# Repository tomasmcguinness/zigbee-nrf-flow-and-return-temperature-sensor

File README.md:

# Zigbee Flow and Return Temperature Sensor on nRF52840

A Zigbee Sensor designed to monitor flow and return temperatures. The sensor provides two temperature sensor probes in a single unit. It can be used to monitor a boiler's flow and return temperatures or the difference between the tails of a radiator.

It uses two NTC Thermistors, which can be attached to the flow and return pipes on whatever you wish to measure; radiator tails, boiler flow and return, hot water cylinder. 

Battery powered, this sensor should run for over about a year and a half on a coin battery or around ten years on a 2000mAh battery.

> [!IMPORTANT] 
> This is still a work in progress. I have included a short list of items at the end of this README

## Parts

* 1 x Seeed XIAO nRF52840
* 2 x 10kΩ 0.1% resistors
* 2 x NTC Thermistors (I use these TT0P-10KC3-T105-1500)
* 1 x push button

## Wiring

In the diagram below, you would replace the two 10kΩ thermistor that are not on the breadboard with the actual probes

## Compiling 

This code has been developed using NCS (nRF Connect Software), with pin outs and battery reading chosen for the Seeed XIAO nrf52840. It should run on any nRF52840 with some tweaking. There is an overlay included for the nRF52840DK, which I use for development.

To compile, run the following command in an `nRF Connect` terminal. The pristine build (-p) flag isn't always necessary.

```
west build -b xiao_ble -p
```

## Flashing

The XIAO board can be flashed using two methods. The first is done using the factory installed bootloader. The second is done using a J-Link programmer. I have a J-Link programmer, so that's the method I've been using.

### UF2

> [!CAUTION] 
> Whilst this method *should* work, I haven't have any success! I want to make this project accessible to those without a J-Link, so I will dedicate time to it.

First, connect the board via USB to your computer. Next, double click the Reset button. A new USB drive should appear.

The compilation process will generate a UF2 firmware file and it will be be located here:

```
zigbee-nrf-flow-and-return-temperature-sensor\build\zigbee-nrf-flow-and-return-temperature-sensor\zephyr\zephyr.uf2
```

Just copy and paste this file onto the USB drive and the application *should* start. 

### J-Link

If you have a J-Link programmer, connect the board and run this command.

```
west flash
```

## Pairing

Once you have flashed the nRF52840 and powered it up, it will enter pairing mode. You can then add it to your Zigbee network using your usual method.

# NTC Thermistors

My Zigbee sensor was build with the TT0P-10KC3-T105-1500 probes, as I have already mentioned. These have a nominal resistance of 10kΩ @ 25°C and have a beta value of 3977. The relevant definitions in the code are here.

```
#define THERMISTORNOMINAL 10000
#define TEMPERATURENOMINAL 25
#define BCOEFFICIENT 3977
#define SERIESRESISTOR 10000
```

> [!NOTE] 
> If you want to use a different thermistor, you can change these values. I plan on making these configurable via the project, but for now you will need to change them directly in code.

# GPIOs

There several GPIOs configured by this project. These have been picked for the Seeed XIAO nRF52840 board.

| GPIO  | Usage |
| ------------- | ------------- |
| P0.03 | ADC (AIN1) pin for Probe 1  |
| P0.29 | ADC (AIN5) pin for Probe 2  |
| P0.28 | Power for the voltage dividers connected to the NTC temperature probes |
| P1.13 | Reset pin. Apply high for 10 seconds to reset the Zigbee configuration | 

# Zigbee ZCL

In order to maintain compatability, this sensor uses standard ZCL clusters rather.

There are three Endpoints 1, 5 & 7

Endpoint 1 contains the Basic cluster, the Identify Cluster and the Power Configuration Cluster.
Endpoint 5 contains a Temperature Measurement Cluster
Endpoint 7 contains a Temperature Measurement Cluster

# Home Assistant

I have tested my sensor on HomeAssistant using the ZHA integration and it displays pretty well. 

Unfortunately, the probe names are terrible.

```
sensor.coldbear_fart_sensor_temperature
sensor.coldbear_fart_sensor_temperature_2
```

I have tried to make a ZHA "Quirk" to display the probes like this:

```
sensor.coldbear_fart_sensor_flow_temperature
sensor.coldbear_fart_sensor_return_temperature
```

but I haven't had any success yet making it work how I want. I have included my work in progress in the project.

# Battery Life

I've invested a lot of time to try and ensure long battery life and I think I've gotten it to over a year on a coin battery! Average consumption is around 16µA

I've written quite a few blog posts detailing the journey, which are up on my blog. You can start here:

https://tomasmcguinness.com/2024/12/19/reducing-power-consumption-in-my-nrf52840-zigbee-sensor-with-the-help-of-a-nordic-semiconductors-power-profiler-ii-kit/

# Setup

Once powered up, you can add the device to your Zigbee network as you would any other Zigbee device.

# PCB

Using KiCAD, I have designed a PCB for this code. 

## V2
A mix of SMD and throughhole mountings, this revision fixes the traces for the reset button (issue in V1) and uses updated footprints for the JST connectors.

> [!CAUTION]
> The battery connections on this PCB are just very difficult to make. I've tried on three different boards, but I've not managed to power the XIAO using the battery terminal. If you had a finer soldering iron, you might have better luck.

## V3
To work around the battery terminal issue and make it easier to for amateurs like myself to solder, V3 has switched to a socket mount for the XIAO board. I also hope to use pogo pins to make the battery connections.

> [!NOTE]
> As of the 15th Feb 2025, I am waiting on the first fabricated versions of this board to verify the socket and pogo pin design will work. 

## V4
This is incomplete. The goal is to move to SMD mounting compleletely and introduce a CR2032 battery holder to make the unit complete. It's present in the PCB-V4 branch.

> [!CAUTION]
> V4 is a work in progress and not ready for use!

All the external connections for NTC probes and battery are via JST connectors.

If you are interested in buying a PCB, do let me know. If there is enough interest, I can place a bulk order.

# Support

If you want to support this project, please consider buying me a coffee!

# Next Steps

* [x] ~~Fix reset button PCB traces~~
* [x] ~~Use reset button to reverse probes i.e. swap readings~~
* [ ] Indicate when probes are swapped
* [ ] Confirm long-term reliability
* [ ] Ensure battery life

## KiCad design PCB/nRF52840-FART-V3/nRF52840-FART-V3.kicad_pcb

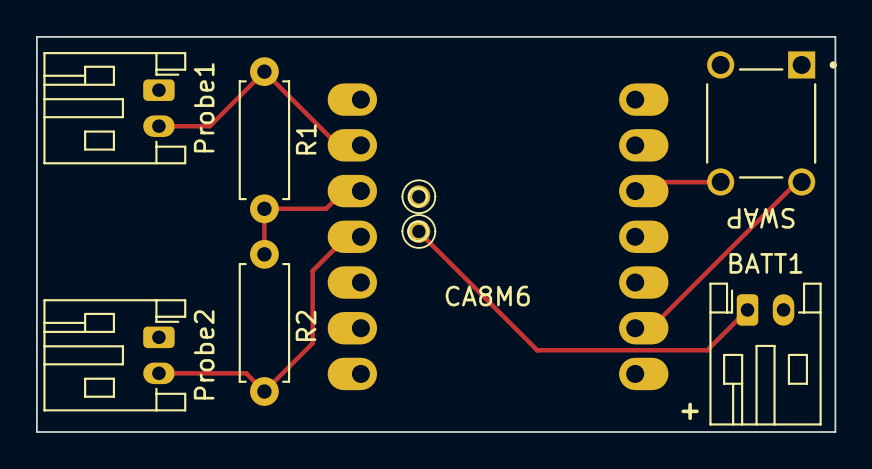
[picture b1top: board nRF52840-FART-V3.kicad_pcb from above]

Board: 2 copper layers, 44.4 x 22.0 mm, 9 parts (0 on the bottom side), 7 nets.

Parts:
BATT1: Conn_01x02_Pin; JST_PH_S2B-PH-K_1x02_P2.00mm_Horizontal
J1, J2: 0914-3-15-20-77-14-11-0; 0914315207714110
Probe1, Probe2: Conn_01x02_Pin; JST_PH_S2B-PH-K_1x02_P2.00mm_Horizontal
R1, R2: 10K; R_Axial_DIN0207_L6.3mm_D2.5mm_P7.62mm_Horizontal
S1: TS02-66-55-BK-100-LCR-D; SW_TS02-66-55-BK-100-LCR-D
U1: xiao-ble; xiao-ble-tht

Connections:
+3.3V: S1.4, U1.12 (3V3)
+BATT: BATT1.1, J2.1
/dividerPower: R1.2, R2.2, U1.3 (A10/0.28)
/p1reading: Probe1.2, R1.1, U1.2 (A4/0.03_H)
/p2reading: Probe2.2, R2.1, U1.4 (A11/0.29)
/reset: S1.2, U1.9 (A7_SCK/1.13)
GND: BATT1.2, J1.1, Probe1.1, Probe2.1

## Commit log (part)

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2025-01-20 Initial checkin
2025-01-21 Clean up some of the battery code and rename a few things. Remove the battery.c and .h files.
2025-01-21 Fix up the variable sizes so they are consistent. Add 2nd buffer for ADC reads to separate battery from temperature.
2025-01-21 Remove vbatt and add comment about origin of battery percentage method
2025-01-21 Use same overlay name as Zephyr
2025-01-22 README updates
2025-01-23 Move to an app_loop instead of two threads. This is to improve stability.
2025-01-23 Add necessary changes to the DK overlay for testing.
2025-01-25 Move code to its own folder
2025-01-25 Add Quirks file
2025-01-25 Add a Fritz file
2025-01-25 Code cleanup. Move .gitignore to right place.
2025-01-26 Remove use of bufid in the app loop calls. Cancel an existing alarm. Free the bufid too.
2025-01-27 Add some cancel alarm calls and check status codes to try and improve long term stability
2025-01-27 Some new KiCAD backups.
2025-01-28 v0.2 of the PCB
2025-02-06 Update README.md
    Mark PCB traces as fixed
2025-02-09 KiCad backups
2025-02-09 Tweaked the overlay for the DK
2025-02-09 Add timer callback for swap button behaviour. Start changes for NVS storage of swap setting.
2025-02-12 Initial code to swap probes, but doesn't compile!
2025-02-12 New PCB designs
2025-02-14 Compilation tweaks
2025-02-14 Add red and gren LED configuration
2025-02-17 Remove V4 from main as it's not ready.
2025-06-06 Tweaks to the PCB design
2025-07-24 Fix reset button configuration.
2025-07-24 More messing with the PCB
2025-07-25 Switch power off gpio0/14 as that's LED2 on the DK
2025-07-25 Remove dead method
2025-07-25 Add the build folder to ignore
